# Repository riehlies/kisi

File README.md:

# kisi – quick signal and power integrity checks for KiCad

kisi reads a KiCad layout (`.kicad_pcb` + `.kicad_pro`) and checks trace impedance, high-speed channels
(loss, return loss, TDR, vias, crosstalk, skew, eye) and power delivery (regulator chain, DC IR drop,
PDN impedance, temperature estimate) – in the browser, with no installation and no setup beyond the board file.

**[Try it in your browser](https://riehlies.github.io/kisi/)** with two example boards, or open your own board
(it is processed locally and never uploaded).

> **Status.** kisi is a quick project, meant to be helpful: a fast check of a board without long setup times.
> Results are estimates for design checks, without any warranty of correctness – not a replacement for
> sign-off simulation or measurement. The individual tools – impedance map with a 2D field solver, TDR and loss
> per net, via model, crosstalk scan, power tree, IR drop, PDN per IC, temperature estimate – are useful on their
> own. kisi stays a fast linear checker – IBIS, AMI and equalisers are out of scope; for sign-off, export the
> channel to PyBERT or a circuit simulator ([why kisi is fast, and its scope](docs/models.md#why-kisi-is-small-and-fast)).

## What you get
- **Impedance:** every track against its target (from net class names such as `50Z`, `90Z_Diff`), with formulas
  in a second and the 2D field solver on demand; impedance along the path, loss, TDR, vias and crosstalk per net;
  every impedance and via result with its accuracy level (field solver, formula, estimate) and typical deviation;
  optionally fab stackup templates as a what-if for all views and the impedance band for manufacturing tolerances
  ([Fab stackups and tolerances](docs/preparing-a-board.md#fab-stackups-and-tolerances-option)).
- **Channel:** buses and device-to-device lanes through series resistors and AC-coupling capacitors, checked
  against interface profiles (PCIe, USB, DDR, LVDS, Ethernet, …) on loss, return loss, skew and a linear eye;
  differential pairs as 4-ports, multi-drop lines at every receiver, connectors with the channel behind them; a
  lane or a whole bus exported as SPICE subcircuits, Touchstone and a KiCad project for circuit simulators.
- **Preparation:** "Prepare PCB" is a checklist of what the board file lacks per category (impedance, channel,
  power): forms for the simple values, Apply per step, and `<board>.kisi.json` saved at the end; the kisi-prepare
  skill does the datasheet research.
- **Power:** the regulator chain and power flow from fields on the parts (`PI_REG`, `PI_LOAD`), DC voltage drop
  per rail and in the ground return, a losses map, a temperature estimate of the board and its parts, and the PDN
  impedance seen from every IC with recommendations.

<table>
<tr><td width="50%" valign="top"><br><b>Net detail:</b> impedance along the path, loss, TDR with the vias as physics-based models, skew of pairs and crosstalk from the neighbouring tracks – for every net with a target</td><td width="50%" valign="top"><br><b>Channel check:</b> buses and lanes from IC to IC or to a connector through series resistors and AC-coupling capacitors, judged against interface profiles on loss, return loss, skew and a linear eye – pairs as 4-ports with mode conversion, multi-drop lines per receiver (at a connector with the end and the channel behind it that you set)</td></tr>
<tr><td width="50%" valign="top"><br><b>Power flow:</b> from the supply inputs through every regulator to the loads, with regulator, shunt and copper losses</td><td width="50%" valign="top"><br><b>Voltage drop and PDN:</b> DC drop and current density on every layer of a rail, and its impedance seen from an IC with the decoupling capacitors ranked by loop inductance</td></tr>
<tr><td width="50%" valign="top"><br><b>Temperature (estimate):</b> the board's temperature per layer from the losses, the hottest parts with their junction temperature and the heat through the vias</td><td width="50%" valign="top"><br><b>Parts at temperature:</b> junction and case temperature against Tj max, with the thermal resistances used and where they come from (datasheet or package estimate)</td></tr>
</table>

## Quick start
- **Browser:** the [live version](https://riehlies.github.io/kisi/), or `kisi.html` from the
  [latest release](https://github.com/riehlies/kisi/releases/latest), offline. Drop the `.kicad_pcb` with the
  `.kicad_pro` (and `<board>.kisi.json` if there is one). KiCad 6 to 10.
- **KiCad:** the plugin `kisi-kicad-<version>.zip` from the release (KiCad's Plugin and Content Manager → *Install
  from File…*) adds a button to the PCB editor that opens the board in the viewer, with its `<board>.kisi.json`,
  and saves that file from the viewer directly next to the board – see [Getting started](docs/getting-started.md#from-kicad-the-plugin).
- **Command line** for scripts, CI and agents (Node.js ≥ 18; every command prints JSON):
  ```sh
  curl -fsSLO https://github.com/riehlies/kisi/releases/latest/download/kisi.mjs
  node kisi.mjs gaps   board.kicad_pcb     # what the analyses miss
  node kisi.mjs check  board.kicad_pcb     # channel check of all interfaces
  ```
- **Agents:** Claude Code `/plugin marketplace add riehlies/kisi` – the skills *kisi-prepare* (research missing
  data into `<board>.kisi.json`) and *kisi-si-pi-review*; other agents can follow the same `SKILL.md` files.

## Documentation
- [Getting started](docs/getting-started.md) – release files, the viewer's views, first commands
- [Preparing a board](docs/preparing-a-board.md) – the gap list, `<board>.kisi.json`, a worked example
- [Field and kisi.json reference](docs/reference.md) – net class names, `PI_*` fields, every kisi.json key
- [Models and limits](docs/models.md) – how kisi computes, accuracy, validation, estimates
- [CLI reference](docs/cli.md) – every command and option
- [Using kisi with agents](docs/agents.md) – skills and setup

All of it as one PDF: `kisi-docs.pdf` on every [release](https://github.com/riehlies/kisi/releases/latest).

## Limits
- The channel check is a first look: linear transmitter and receiver from the interface profile, no IBIS models,
  equalisation, jitter or noise.
- 2D cross-sections and reduced via and plane models instead of a full-board 3D solution.
- Validated against 620 cross-sections in CST and HFSS cases (field solver and formulas) and against 3D FDTD
  references of vias, pairs and plane cavities, each cross-checked with openEMS and CST; validation against
  measurements is still open. Data the board file lacks defaults to estimates until `<board>.kisi.json` fills
  it in. Details: [Models and limits](docs/models.md).

## Development
Build, checks and rules: [AGENTS.md](AGENTS.md) · structure: [ARCHITECTURE.md](ARCHITECTURE.md) · contributing:
[CONTRIBUTING.md](CONTRIBUTING.md) · planned work: [ROADMAP.md](ROADMAP.md) · field solver upstream:
[UPSTREAM.md](UPSTREAM.md).

## Related tools
- [js_2d_fields](https://github.com/Ttl/js_2d_fields) – Henrik Forstén's 2D field solver in the browser, used by kisi.
- [KiPI](https://github.com/drewsum/KiPI) – power integrity for KiCad (DC drop, PDN impedance, coupled noise).
- [padne](https://github.com/atx/padne) – DC voltage drop of KiCad boards with the finite element method.
- [openEMS](https://www.openems.de) – open 3D FDTD solver, for the cases where a reduced model is not enough.

## Credits
Field solver: [js_2d_fields](https://github.com/Ttl/js_2d_fields) by Henrik Forstén (GPL-3.0).
Example boards in `kisi-examples.html`: [ThunderScope](https://github.com/EEVengers/ThunderScope) Rev5.3 (EEVengers,
hardware under CERN-OHL-P-2.0) and [LibreVNA](https://github.com/jankae/LibreVNA) (Jan Käberich, GPL-3.0), shrunk to
what kisi reads; the licence texts are embedded with them.
Fonts: Barlow, Barlow Semi Condensed and JetBrains Mono (SIL Open Font License 1.1, `web/fonts/`), embedded in the viewer.

## About
kisi is a side project by David Riehl. It started as a visualisation tool for the course *Advanced PCB Design* at
TU Darmstadt and grew into a general check for KiCad boards. It was also an experiment in what current AI models
make possible: kisi was written with an AI coding assistant (Claude, Anthropic) – without it, a tool of this scope
would not have been possible as a side project. Commits made with AI help say so in their `Co-Authored-By` line.

Copyright © 2026 David Riehl and kisi contributors. Licence: GPL-3.0-only (`LICENSE`).

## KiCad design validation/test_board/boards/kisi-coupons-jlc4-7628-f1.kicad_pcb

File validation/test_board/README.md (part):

# Measurement coupons (test boards)

Status: **design v3, prepared, not ordered.** First order (maintainer, 2026-10-30 / 31): two JLC 4-layer boards
(100 × 96 and 35 × 156 mm) and one JLC 6-layer board (50 × 132 mm) with 7628 prepreg (section 4,
`make_coupons.py --first-order`). 23 more boards stay generated for
later (JLC 4 / 6 / 8 layers with 7628 prepreg, one Aisler board, JLC 4 / 6 layers with 3313 prepreg). kisi reads all of them, their
impedances are on target with kisi's field solver, the PDN and capacitor coupons have a measurement method and a
component list, and the 3D cases are written (**not run**). The connector is the 2.92 mm Samtec
`292-J-P-EP-ST-EL-01` (40 GHz); its footprint is generated from Samtec's drawing and is a **DRAFT**, and the launch
inside it is parametric, optimised on the board side in a first kisi-fdtd step (|S11| −21 dB at worst to 40 GHz;
the connector's coax not in the model, section 2). **DRC:** KiCad 7 (the workspace has no KiCad 8) on
copies converted to KiCad 7 syntax, zones refilled: no errors, no unconnected items (section 13); the maintainer
reruns it in KiCad 8 / 9. The plan behind this is `../test_board.md`.

Goal: close the loop simulation → measurement for kisi's fast models and the 3D references (`../via_ref`). The same
coupon geometry is measured, computed with kisi-fdtd (cases generated from the same description as the KiCad board)
and with kisi (the board file itself), and all three are de-embedded the same way (IEEE P370-style 2×thru,
`../fdtd/sparam.py`).

What changed in v3 (2026-10-30): the 2.92 mm Samtec connector instead of SMA and a 40 GHz frequency plan
(section 2); the footprint generated from Samtec's drawing with plated screw holes and ground pads on top and bottom;
a parametric launch (tip, taper, pad, coplanar section, ground cut, fence) and its kisi-fdtd cases
(`fdtd/launch_<stackup>/`, `make_coupons.py --launch-cases`); the GND via walls between rows at 1.27 mm instead of
2.54 mm (closed to 40 GHz). The coupons, widths and stackups are unchanged.

What changed in v2 from v1 (commit d7a7ec8): SMA connector and a 26.5 GHz frequency plan; boards split to the JLC price
brackets; every board has its own 2×thru and all connectors are on the top side (via coupons are via–line–via);
an 8-layer set; the thin-prepreg set; PDN coupons (plane cavity, pin field with capacitors) and capacitor coupons
with a component list; a pin-wide launch with a plane opening for the thin prepreg. The single v1 3D result
(`fdtd_ref/`) belonged to the old geometry and is removed.

## 1. Files

| Path | Content |
|---|---|
| `make_coupons.py` | generator: boards, kisi configuration, 3D cases; trace widths from kisi |
| `stackups.json` | stackups with values and sources (JLC 4 / 6 / 8 layers, Aisler assumed, thin prepreg) |
| `connectors.json` | Samtec 2.92 mm edge launch with sources and the drawing's dimensions, footprint parameters (**DRAFT**), launch parameters (to be optimised), layout pitches, via sizes, capacitor land patterns, size limits |
| `boards/<board>.kicad_pcb`, `.kicad_pro` | KiCad 8 boards (KiCad 9 opens them); net classes `50Z`, `100Z_Diff` |
| `boards/kisi_coupons.pretty/`, `boards/fp-lib-table` | the footprints the boards use (the Samtec launch per width, the capacitor land patterns, the IC pin fields), generated with the boards, as a project-local library (`${KIPRJMOD}`): KiCad finds them and DRC's library check matches |
| `boards/<board>.kisi.json` | kisi configuration: dielectric values with sources, class targets and profiles |
| `boards/<board>.manifest.json` | coupons, nets, connectors (J numbers, port order), parts (C/U refs), 3D cases and their cell counts |
| `boards/<stackup>.design.json` | trace widths and the impedance table (kisi formula and field solver) |
| `boards/<board>.kisi_check.json`, `kisi_check.md` | kisi run on every board (section 9) |
| `fdtd/<board key>/*.json` | kisi-fdtd cases, format of `../fdtd/via_cases.py`; run with `../fdtd/run_refs.py` |
| `fdtd/launch_<stackup>/*.json` | launch optimisation cases (section 2) |
| `fdtd_ref/launch_<stackup>/<case>/` | kisi-fdtd results of the launch cases (`kisi.s2p`, `meta.json`; section 2) |
| `check_coupons.py` | runs kisi on the boards → `kisi_check.md` |
| `compare_measured.py` | measured vs kisi vs kisi-fdtd (section 12) |
| `cst_launch.py`, `compare_launch.py`, `README_cst_launch.md` | CST Studio Suite model of the whole connector launch with Samtec's STEP model (not in the repository), compared with kisi-fdtd and Samtec's report (section 2) |

## 2. Connector, launch and frequency plan

### Connector

- **Samtec `292-J-P-EP-ST-EL-01`** (decided 2026-10-30, on the RF group's advice): 50 Ω 2.92 mm (K) jack, edge
  launch, solderless compression mount (field replaceable), performance to **40 GHz**, PCB thickness .040–.100 in
  (1.02–2.54 mm, option `-01`: every board fits, the 2.05 mm 8-layer board included), two #1-72 socket-head screws
  with #1 split washers (1/16 in hex key), **0.5–0.8 in-lb**; intermates with 3.5 mm and SMA. Why: orderable at
  DigiKey (in stock, maintainer 2026-10-30) and Mouser, solderless and reusable. Price 52.65 USD for one (Samtec, 2026-10-30). Needed:
  **4** (2 per 2-port coupon, 4 for the 4-port coupons; they move between coupons), a fifth as a spare. Sources and
  the drawing's dimensions: `connectors.json` (`connector`).
- Data from Samtec (supplied by the maintainer 2026-10-30, **not in the repository**: the terms of the SnapMagic
  footprint and the CADENAS STEP model forbid redistributing the models; the drawing is proprietary): drawing
  292-J-P-EP-ST-EL-01-X-MKT rev C, SnapMagic KiCad footprint and symbol, CADENAS STEP model, RF Characterization
  Report (2023-06-01). Samtec has no CST / HFSS model of the part.
- From the drawing and the STEP model: launch pin Ø0.18 mm (.007 in), 0.74 mm beyond the reference plane (the board
  edge), its axis 0.13 mm above the board, in a Ø0.70 mm opening of the body's front lip; the top jaw covers the
  board 5.08 mm deep and 9.53 mm wide, with a slot over the trace (2.67 mm wide from 0.38 mm, 3.18 mm from 0.64 mm,
  open to the top); the lower plate clamps the bottom side; screws 2.79 mm from the edge, ±2.92 mm.

### Footprint (generated, DRAFT)

`make_coupons.py` writes the footprint `kisi_coupons:Samtec_292-J-P-EP-ST-EL-01_EdgeLaunch_W<launch width>` (one per
launch geometry) from the parameters in `connectors.json` (`footprint`), on the boards and into the project-local
library `boards/kisi_coupons.pretty` (with `boards/fp-lib-table`, `${KIPRJMOD}`); its geometry follows Samtec's
drawing (sheet 2, "recommended footprint"):

| Feature | Drawing | Footprint |
|---|---|---|
| Screw holes | 2X Ø.0810 in, 2X .1100 in from the edge, 2X .230 in apart | Ø2.06 mm plated, GND, 2.79 mm from the edge, ±2.92 mm; Ø2.7 mm pad on every copper layer |
| Ground pads | .2550 in deep, .414 in overall, inner edges .114 in apart, 45° chamfers from .205 in to .314 in, fingers .025 in deep, .0220 in apart at the edge | the same, on the top and bottom copper (where the jaws clamp; Samtec's model has them on every layer: our planes do that inside, and PWR islands stay clear), mask open both sides (+0.05 mm) |
| Signal pad | .0205 in wide (0.52 mm), tip .0090 in (0.23 mm) | our launch (below): by default the launch width to the edge; Samtec's 0.23 mm tip tapering over 0.85 mm (taper length from the SnapMagic model) as an option |
| Edge | copper to the edge | pulled back 0.2 mm (JLC rule): the pin still rests 0.54 mm on the tip, the lip 0.18 mm on the fingers |
| Body, courtyard | body .375 in wide | Fab: body 9.53 mm wide, 5.08 mm on the board, 11.57 mm outside; courtyard ±5.51 mm, 6.73 mm on the board |

The generator checks that no copper of another net lies under the ground pads (top / bottom) and that PWR islands
keep clear of the screw holes. The finger contour (0.84 mm half-width at 0.64 mm, 0.35 mm at 0.45 mm) and the taper
length come from the SnapMagic footprint, not from dimensions on the drawing.

### Launch (parametric, first optimisation step)

Samtec's general signal pad (0.52 mm wide, 1.19 mm from the ground pads, 6.48 mm long) is 43.5 Ω on the 0.21 mm 7628
prepreg (kisi field solver): Samtec states the footprint is not optimised for electrical performance. Our launch
inside the same ground pads (`connectors.json` `launch`, `null` = the stackup's designed launch); the defaults are the
best of the first kisi-fdtd runs below:

| Parameter | Default (7628 / 3313) | Meaning |
|---|---|---|
| `tip_w`, `taper_len` | `null` (the launch width to the edge), 0.85 mm | an optional narrower tip at the edge tapering to the pad width (Samtec: 0.23 mm; a sweep point) |
| `pad_w`, `pad_len`, `pad_gap` | = launch: 0.315 mm, no extra pad, gap 0.3 mm / 0.255 mm, gap 0.105 mm | an optional wider pad (Samtec: 0.52 mm × 6.48 mm, gap 1.19 mm) |
| `w`, `gap` (design) | 0.315 / 0.3 mm (50.0 Ω) / 0.255 / 0.105 mm with the In1 opening (50.05 Ω) | the grounded coplanar launch |
| `launch_length` | 6.48 mm | to the end of the ground pads, then the coupon's 50 Ω line |
| `gnd_cut` | none / the design's In1 opening (0.465 mm) over the whole launch | an opening in the first plane under the tip / pad |
| `fence` | 0.55 mm pitch from 0.5 mm, two rows 0.4 / 1.2 mm off the gap, none within 0.45 mm of a screw hole | GND vias into all planes (0.55 mm: hole-to-hole 0.25 mm, the DRC minimum) |

The pin (Ø0.18 mm) rests on the 0.315 mm launch on 7628 and on the 0.255 mm launch on 3313. The top ground is the
union of the Samtec ground pads and the coplanar pours. The outer fence row (1.66 mm off the centre) lies in the
ground pads, where the mask is open and the jaw edge (slot wall at 1.59 mm) presses: open via holes in the contact
area are harmless electrically; if the jaw should sit on flat copper, order plugged vias or move that row inside
1.45 mm (a fence parameter). Change the values and run `make_coupons.py --reuse-design` (the boards, manifests and 3D
cases are rewritten in seconds).

### Launch optimisation (kisi-fdtd)

`make_coupons.py --launch-cases jlc4_7628 [--fdtd-exe …]` writes `fdtd/launch_jlc4_7628/`: the board from its edge to
the end of the launch plus 2.5 mm of the 50 Ω microstrip, the ground pads top and bottom, the plated screw holes,
the fence, the mask, port 1 a lumped 50 Ω port at the edge (tip to In1; under a ground cut In1 keeps a 0.25 mm strip
at the edge), port 2 at the end of the microstrip. The 7628 top prepreg is the same on the 4-, 6- and 8-layer boards,
so one stackup serves the first order (the planes below In1 differ; check the result on the 6- and 8-layer stacks).

- **Not modelled:** the connector's coax (kisi-fdtd has z-directed cylinders and horizontal sheets only): the edge
  port stands in for it, so the cases optimise the board side. `pin` adds the pin as a strip on the tip; `body` the
  top jaw (sheets with its slot, posts, the lip). CST with Samtec's STEP model and a waveguide port on the 2.92 mm
  interface checks the whole transition: `cst_launch.py` builds it (`README_cst_launch.md`; the connector from primitives with the STEP's dimensions; a first run with the imported STEP failed, to be run again).
- **Target:** |S11| < −20 dB to 40 GHz for one launch (Samtec's own optimised fixture on MT40: −23 to −25 dB for one
  connector with 500 mil of trace, report 2023-06-01).
- **Results (2026-10-30, `fdtd_ref/launch_jlc4_7628/`):**

  | Case | What | max \|S11\| 0.5–40 GHz | \|S11\| at 10 / 20 / 30 / 40 GHz | \|S21\| at 40 GHz (≈ 9 mm) |
  |---|---|---|---|---|
  | `default` | launch width to the edge, fence 0.55 mm | **−21.0 dB** at 36.5 GHz | −29.8 / −28.5 / −28.6 / −25.0 dB | −0.75 dB |
  | `notip_f05` | the same, fence 0.5 mm | −21.0 dB at 36.4 GHz | −29.9 / −28.5 / −28.7 / −25.0 dB | −0.75 dB |
  | `notip_f08` | the same, fence 0.8 mm from 0.8 mm (first draft) | −18.9 dB at 36.8 GHz | −29.9 / −28.4 / −29.1 / −22.2 dB | −0.84 dB |
  | `tip023_f08` | Samtec's 0.23 mm tip, fence 0.8 mm | −15.7 dB at 37.2 GHz | −38.0 / −30.5 / −19.9 / −15.7 dB | −0.93 dB |
  | `tip023_pin_f08` | the same with the pin | −16.8 dB at 37.0 GHz | −35.6 / −33.2 / −22.1 / −17.3 dB | −0.90 dB |
  | `samtec` | Samtec's pad (0.52 mm, gap 1.19 mm, 0.23 mm tip), fence 0.8 mm | −14.6 dB at 24.8 GHz | −26.6 / −19.7 / −19.5 / −22.0 dB | −1.19 dB |
  | `default_body`, `samtec_cut` | with the jaw; Samtec's pad over an In1 cut | not valid yet / not run | | |

  Reading: our 50 Ω coplanar launch inside the Samtec pads meets the target on the board side (−21.0 dB worst). The
  0.8 mm fence left narrow \|S21\| dips at 25.5, 27, 35.5 and 37.5 GHz (resonances of the fence / screw-hole region);
  0.55 mm from 0.5 mm removes them (and halves the ringing: 12 800 instead of 23 200 steps). Samtec's 0.23 mm tip is
  inductive on 7628 even with the pin over it (−16.8 dB); Samtec's general pad is not usable on the 0.21 mm prepreg
  (−14.6 dB, and its sparse fence – the rows move out to the screw holes – lets the plane-pair mode carry power
  away: \|S21\| −2 dB already at 1 GHz). Values below about 2 GHz are limited by the edge port (−24 dB at 1 GHz on
  every case). `default_body` (the jaw) ran twice (as `ours_body`) and is **not valid yet**: port 1 sees a near short
  (\|S11\| about 0 dB at low frequency, \|S21\| −30 dB at 1 GHz rising to −2.7 dB at 40 GHz), also after moving the
  jaw's underside to the copper height and its top off the domain boundary – the jaw approximation needs debugging.
- **Other stacks** (the `default` case written with `launch_case` for each, not stored): jlc6-7628 and jlc8-7628
  give the same −21.0 dB at 36.5 GHz (the same 7628 top prepreg; the planes below In1 do not matter here), so the
  first order's 6-layer boards share the 4-layer launch. jlc4-3313 (the pin-wide 0.255 mm launch over the In1
  opening): −16.7 dB at 34.5 GHz – to be optimised before a 3313 order.
- **Run time:** 0.9–1.0 M cells: 120–680 s per case on this workspace (2 vCPUs shared with other jobs); the jaw cases
  (2.1–2.3 M cells) about 950 s.
- **Next:** fix the jaw case; the coplanar `gap` 0.2–0.4 mm with `w` re-solved for 50 Ω, `launch_length` 3–6.48 mm, a
  cut in In1 under the edge (0.3–0.8 mm wide, 0.3–1.0 mm long), the fence row offset; the 6- and 8-layer stacks; the
  thin-prepreg (3313) launch (`--launch-cases jlc4_3313`); then CST with the STEP model for the whole connector.

### Frequency plan (2.92 mm, 40 GHz)

kisi's stub resonance for the stubbed vias (`kisi_check.md`):

| Coupon | Stub | kisi stub resonance | In the 40 GHz band? | v3 |
|---|---|---|---|---|
| 6 layers VLV_L3, SL_L3 (L1 → In2, stub to L6) | 0.88 mm (3313: 0.82) | 32.4 GHz (34.5) | **yes** (v2: no) | the notch is now measured on the 6-layer board too (PNA-X, PNA) |
| 6 layers DIFF_SL, BS_L3L4 (inner exits) | 0.65–0.88 mm | 24.5–38 GHz | yes (v2: partly) | coupling coupons, read in the time domain |
| 8 layers VLV_L3, SL_L3 (L1 → In2, stub to L8, 2.05 mm board) | 1.42 mm | 19.8 GHz | yes | inside the band of every VNA, the 20 GHz ENA included |
| 8 layers E_L1L3 (pair, stub to L8) | 1.42 mm | 22.1 GHz | yes | differential stub notch |
| 8 layers VLV_L6 (L1 → In5, stub to L8) | 0.60 mm | 38.5 GHz | **yes**, at the top (v2: no) | short-stub reference; its notch now just inside the band |

- **2.0 mm 8-layer board:** with 40 GHz, a 1.6 mm 8-layer board (about 1.1 mm of stub, notch near 25 GHz) would now be
  inside the band too; the 2.0 mm board stays (a lower, deeper notch that the 20 GHz ENA sees as well; within the
  connector's 2.54 mm limit). Not changed.
- **Row walls:** at 2.54 mm the GND via walls between rows open near 28 GHz (pitch = λ/2 in FR-4); v3 uses 1.27 mm
  (λ/2 near 56 GHz). The launch fence (0.8 mm, below λ/4 at 40 GHz) and the CPWG fence (1.0 mm, below λ/2) stay.
- **TRL:** LINE_27 (ΔL 2 mm) reaches 160° near 37 GHz; the multiline set (ΔL 2 / 5 / 10 / 25 / 75 mm) stays usable to
  40 GHz with LINE_30 and LINE_50.
- **3D cases:** already computed to 40 GHz (section 7), unchanged.
- Everything else (lines, through vias, return path, pairs without stubs, coupling) has no stub resonance below
  40 GHz; the plane cavities resonate at 1.4–3.2 GHz (measured to 8 GHz).

## 3. Stackups

Values fetched on 2026-10-22; sources in `stackups.json` (key `sources`): thicknesses from JLC's impedance-template
data ([gsuberland/jlcpcb_autogenerated_stackups](https://github.com/gsuberland/jlcpcb_autogenerated_stackups), commit
9c8b685), 7628 / 3313 / 2116 εr from [JLC capabilities](https://jlcpcb.com/capabilities/pcb-capabilities), core εr
4.6 from [JITX's JLC materials](https://docs.jitx.com/en/latest/_modules/jitxlib/jlcpcb/materials.html), tan δ 0.02
assumed (not published), mask εr 3.8 and 1.2 mil from the
[JLC impedance calculator guide](https://jlcpcb.com/help/article/user-guide-to-the-jlcpcb-impedance-calculator).

| Stackup | Order | Dielectrics L1 → bottom (mm) | Copper | Planes / signal layers |
|---|---|---|---|---|
| **JLC04161H-7628** | first | 7628 0.2104 · core 1.065 · 7628 0.2104; 1.586 total | 1 oz outer, 0.5 oz inner | GND In1, In2 (PDN: PWR islands on In2) / L1, L4 |
| **JLC06161H-7628** | first | 7628 0.2104 · core 0.4 · 7628 0.2104 · core 0.4 · 7628 0.2104; 1.562 | same | In1, In4 / L1, In2, In3, L6 |
| **JLC08201H-7628** | first | 7628 0.2104 · core 0.35 · 7628 · core 0.35 · 7628 · core 0.35 · 7628; 2.053 | same | In1, In3, In4, In6 (PDN: PWR islands on In3 over In4, 0.35 mm) / L1, In2, In5, L8 |
| Aisler 4 layers 1.6 mm (**assumed**) | first | prepreg 0.2 · core 1.2 · prepreg 0.2 (εr 4.3 / 4.5 / 4.3) | 35 µm | as JLC 4 layers |
| **JLC04161H-3313** | second | 3313 0.0994 · core 1.265 · 3313 0.0994; 1.564 | 1 oz / 0.5 oz | as JLC 4 layers |
| **JLC06161H-3313** | second | 3313 0.0994 · core 0.55 · 2116 0.1164 · core 0.55 · 3313 0.0994; 1.546 | same | as JLC 6 layers |
| JLC08161H-2116 | – | in `stackups.json`, not generated (1.6 mm 8 layers: stub only about 1.1 mm) | | |

The 7628 top prepreg is the same on the 4-, 6- and 8-layer boards (and on LibreVNA), so the launch and the L1 lines
are identical on all first-order JLC boards: a build-to-build check. The Aisler stack is the generic `s4` of the
3D references until Aisler sales give the real one; its line and cavity coupons extract it.

## 4. Boards

### First order (maintainer, 2026-10-30 / 31)

Only JLC 4 layers (JLC04161H-7628) and JLC 6 layers (JLC06161H-7628), three boards; the other boards below stay
generated for later. An edge launch takes 12 mm of board edge per connector and side (rows of 12 mm, 4-port rows
24 mm), so a 96 mm board holds 16 connector positions: the 4-layer coupons need 38 (with a 2×thru on each board) and
need two boards, one of them above the 100 × 100 mm bracket; the 6-layer board is one board above the 50 × 50 mm
bracket (accepted). One 2×thru per board (PAIR is the E coupons' fixture). `make_coupons.py --first-order` writes
only these. Sizes are the bounding boxes of the stepped outlines (what JLC's calculator asks for):

| Board | Size (mm) | Thickness | Coupon | What | 3D reference cases |
|---|---|---|---|---|---|
| **jlc4-7628-f1** | **100 × 96** | 1.59 mm | THRU | 2×thru L1 (fixture of this board) | thru_s4_L1 |
| | | | CPWG_25, CPWG_50 | grounded coplanar line, L and 2L (εr, tan δ, roughness by line–line) | T_vna6_cpwg_10 / _20 |
| | | | XT_MS | edge-coupled microstrip aggressor / victim (4-port) | T_ts6_xt_ms_s10 |
| | | | G_CAV | plane cavity 50 × 30 mm, two ports (shunt-thru) | G_pp100 / pp200 |
| **jlc4-7628-f2** | **35 × 156** | 1.59 mm | THRU | 2×thru L1 | thru_s4_L1 |
| | | | A0800, A1000, A1200 | coax section L1 → L4 → L1, antipad Ø0.8 / 1.0 / 1.2, 4 GND vias at 1 mm | A_s4_d300_ap800 / ap1000 (1.2: none) |
| | | | D_S0p7, D_S2p0, D_NONE | return via 0.7 / 2 mm from each via / none, L1 (ref In1) → L4 (ref In2) | D_s8_stitch_0p5 / 2p0 / none |
| | | | PAIR | pair 2×thru at the 1.0 mm via pitch (fixture of E) | – |
| | | | E_R_G2, E_R_G0 | differential via pair L1 → L4 → L1, round antipads, 2 / 0 GND vias (4-port) | E_s8_L1L8_p1000_round_g2 / g0 |
| **jlc6-7628-f1** | **50 × 132** | 1.56 mm | THRU | 2×thru L1 | thru_s4_L1 |
| | | | SL_L3, VLV_L3 | 25 mm stripline on In2 (L3) and the 5 mm version: line–line = the stripline 2×thru; VLV_L3 is also the via with stub (to L6, notch 32 GHz) | T_ts6_sl_10 / _20, B_ts6_L1L3_stub, B_s8_L1L3_stub_d300 |
| | | | B_L1L6 | through via without stub | B_ts6_L1L6, B_s8_L1L8_d300 |
| | | | PAIR, E_R_G2 | pair 2×thru; pair L1 → L6 → L1, 2 GND vias | E_s8_L1L8_p1000_round_g2 |
| | | | D_S0p7, D_S2p0, D_NONE | return via 0.7 / 2 mm / none, L1 (ref In1) → L6 (ref In4) | D_s8_stitch_0p5 / 2p0 / none |

The lines, the coupling coupon and the cavity share the 100 mm-wide board (the cavity row sets its width anyway);
the via groups stay together on one board, so A, D and E are compared within one panel.

- **0.5 mm return via:** made at 0.7 mm. With the 0.3 / 0.6 mm vias the pads would overlap at 0.5 mm (the 3D
  reference D_s8_stitch_0p5 is idealised: a bare barrel); 0.7 mm keeps 0.1 mm between the pads (JLC) and puts the
  GND barrel just outside the Ø0.8 antipad. The 3D case of D_S0p7 has the 0.7 mm geometry.
- **8-layer board:** the 6-layer stub notch (VLV_L3, kisi 32.4 GHz; 3D reference B_ts6_L1L3_stub) is inside the
  40 GHz band, so the first order measures a stub notch without the 8-layer board. The 8-layer long-stub board
  (notch near 20 GHz, deeper, also within the 20 GHz ENA) stays for later.
- **Later (generated, not in the first order):** the PDN loop and capacitor coupons (assembly: jlc4-7628-p, -d,
  jlc8-7628-p), Aisler, the 3313 thin-prepreg boards, the 8-layer boards, and the other JLC 4 / 6-layer coupons
  (microstrip lines and the TRL set, oval antipad, D at 1 / 3.5 mm, broadside, stripline pair: jlc4-7628-a … -d,
  jlc6-7628-a … -d).
- **DRC** (KiCad 7 on converted copies, section 13): no errors, no unconnected items on the three boards.

### All boards

Limits (maintainer, 2026-10-22, JLC price brackets): 4 layers ≤ 100 × 100 mm, 6 and 8 layers ≤ 50 × 50 mm; the
generator refuses a JLC board that exceeds them. Aisler charges by area: one dense board of 35 mm rows.
Rows are sorted by length (a stepped outline); a row is one coupon from edge to edge, or two coupons side by side
with their ports on the outer edges (PDN coupons). 2-port rows are 12 mm, 4-port rows 24 mm (two connectors per
edge, 12.7 mm apart). GND via walls (1.27 mm, through all layers; v2: 2.54 mm) run along every row boundary and along the
exposed step edges. Through vias only, drill 0.3 / pad 0.6 mm, inner non-functional pads removed. Antipads, island
clearances and the launch openings are KiCad keep-out rule areas, so a refill reproduces them. Bottom silk: board
name, template, date and JLC's order-number placeholder `JLCJLCJLCJLC`.

| Board | Layers | Size (mm) | Coupons |
|---|---|---|---|
| **kisi-coupons-jlc4-7628-a** | 4 | 100 × 96 | THRU, LINE_27, LINE_30, LINE_50, LINE_100, REFLECT, CPWG_25, CPWG_50 |
| **kisi-coupons-jlc4-7628-b** | 4 | 35 × 96 | THRU, A0800, A1000, A1200, D_S1p0, D_S2p0, D_S3p5, D_NONE |
| **kisi-coupons-jlc4-7628-c** | 4 | 35 × 96 | PAIR, E_R_G2, E_O_G2, E_R_G0 |
| **kisi-coupons-jlc4-7628-d** | 4 | 50 × 96 | THRU, CAPZ_0402, CAPZ_0603, CAPZ_0805, XT_MS, DIFF_MS |
| **kisi-coupons-jlc4-7628-p** | 4 | 100 × 96 | THRU, G_CAV, H_D2, H_D5, H_D10, H_D20 |
| **kisi-coupons-jlc6-7628-a** | 6 | 35 × 48 | THRU, B_L1L6, D_S1, D_NONE |
| **kisi-coupons-jlc6-7628-b** | 6 | 50 × 48 | THRU, VLV_L3, SL_L3, LINE_50 |
| **kisi-coupons-jlc6-7628-c** | 6 | 35 × 48 | PAIR, E_R_G2 |
| **kisi-coupons-jlc6-7628-d** | 6 | 50 × 48 | BS_L3L4, DIFF_SL (no 2×thru: section 5) |
| **kisi-coupons-jlc8-7628-a** | 8 | 50 × 48 | THRU, VLV_L3, B_L1L8, SL_L3 |
| **kisi-coupons-jlc8-7628-b** | 8 | 35 × 48 | THRU, VLV_L6, D_S1, D_NONE |
| **kisi-coupons-jlc8-7628-c** | 8 | 35 × 48 | PAIR, E_L1L8 |
| **kisi-coupons-jlc8-7628-d** | 8 | 35 × 48 | PAIR, E_L1L3 |
| **kisi-coupons-jlc8-7628-p** | 8 | 50 × 48 | H_D2, H_D5, H_D10, H_D2_0603 (no 2×thru: section 5) |
| **kisi-coupons-aisler4-assumed-a** | 4 | 35 × 144 | THRU, LINE_27, LINE_30, LINE_35, A0800, A1000, A1200, D_S1p0, D_S2p0, D_NONE, G_SMALL |
| kisi-coupons-jlc4-3313-a … -d | 4 | as jlc4-7628-a … -d | the same coupons on the thin prepreg (CAPZ: the mounting inductance with 0.1 mm to the plane) |
| kisi-coupons-jlc6-3313-a … -d | 6 | as jlc6-7628-a … -d | the same coupons on the thin prepreg |

Besides the first order (above): 14 JLC 7628 boards and the Aisler board, and 8 JLC 3313 boards, generated for later.

### Coupons

| Coupon | Length (mm) | What | Validates in kisi | 3D reference | 3D window |
|---|---|---|---|---|---|
| THRU | 25 | 2×thru on L1, reference planes 12.5 mm from each edge | fixture of every 2-port coupon on the board; TRL thru | thru_s4_L1 | w10 |
| LINE_27 / 30 / 35 / 50 / 100 | 27–100 | 50 Ω microstrip, ΔL 2 / 5 / 10 / 25 / 75 mm against THRU | εeff, loss per mm, Zc (line–line); multiline TRL | T_ts6_ms | LINE_50 w10 / w20 |
| REFLECT | 30 | two open ends at the reference planes | TRL reflect | – | – |
| CPWG_25, CPWG_50 | 25, 50 | grounded CPW on L1, gap 0.18 mm (LibreVNA), fence 1.0 mm | CPWG Zc and εeff (formula εeff +5 % vs 3D) | T_vna6_cpwg | w10, w20 |
| A0800 / A1000 / A1200 | 30 | via–line–via L1 → L4 → L1 through the plane pair, antipad Ø0.8 / 1.0 / 1.2, 4 GND vias at 1 mm | via ladder: antipad dependence of Z and delay | A_s4_d300_ap800 / ap1000 | wv |
| D_S1p0 / S2p0 / S3p5 / NONE | 35 | L1 (ref In1) → L4 (ref In2) → L1, one GND via at 1 / 2 / 3.5 mm from each via, none | return path of a reference change (GND vias within 3 mm enter the ladder, up to 5 mm an inductance, beyond "missing") | D_s8_stitch_* | wv |
| B_L1L6, B_L1L8 | 30 | through via, no stub (via–line–via on the bottom layer) | via ladder through several planes | B_ts6_L1L6, B_s8_L1L8_d300 | wv |
| VLV_L3 (6, 8 layers), VLV_L6 (8) | 30 | via–line–via to an inner layer, stub to the bottom | junction model, stub capacitance / notch (section 2) | B_*_L1L3_stub, X_s8x2_L1L3_bd | wv |
| SL_L3 | 50 | the same with 25 mm stripline | stripline γ (line–line with VLV_L3: the vias cancel), Zc from the TDR plateau | T_ts6_sl | w10, w20 |
| PAIR | 30 | pair 2×thru on L1 at the 1.0 mm via pitch (100 Ω diff.), 15 mm per side | fixture of the pair coupons on the board | – | w6 |
| E_R_G2 / E_O_G2 / E_R_G0 / E_L1L8 / E_L1L3 | 35 | pair via–line–via, pitch 1.0, round / oval antipads, 2 / 0 GND vias; E_L1L3 with stubs | pair ladder: Sdd21, Zdiff, Scd21, oval antipad, differential stub | E_s8_L1L8_p1000_*, E_s8_L1L3 | wv |
| XT_MS | 50 | 50 Ω aggressor and victim on L1, edge gap = w | NEXT / FEXT (kisi's NEXT 70–80 % high vs 3D) | T_ts6_xt_ms_s10 | wc |
| DIFF_MS, DIFF_SL | 50 | 100 Ω edge-coupled pair on L1 / In2 | Zdiff (TDR plateau), odd-mode εeff | T_ts6_diff_ms / _sl | wc |
| BS_L3L4 | 50 | broadside In2 over In3 | broadside NEXT / FEXT (kisi lists, does not compute yet) | T_ts6_broadside_o0 | wc |
| CAPZ_0402 / 0603 / 0805 | 25 | capacitor footprint in shunt on the 50 Ω line, two GND vias | mounted C, ESR, ESL, mounting inductance, pad capacitance (section 6) | – | w10 (0 Ω) |
| G_CAV, G_SMALL | 100, 35 | PWR island 50 × 30 (Aisler 25 × 18) mm on In2 under In1 (JLC d = 1.065 mm, Aisler assumed 1.2 mm), ports at a corner and the centre | cavity resonances (kisi cavity model ±0.8 % vs 3D), core εr, plane capacitance | G_pp100/200 | wg |
| H_D2 / D5 / D10 / D20, H_D2_0603 | 50 (4 layers), 25 (8) | pin field + one capacitor at 2 / 5 / 10 / 20 mm, PWR island, two shunt-thru ports (section 6) | capacitor loop inductance and Z(f) at the IC (`power --pdn`) | H_s8_cap_* | wh |

The trace widths of every coupon come from `boards/<stackup>.design.json` (section 8). The G coupon's first modes
(magnetic walls, εr 4.6): 1.40 (10), 2.33 (01), 2.72 (11), 2.80 (20) GHz; kisi's cavity model gives 1.398 GHz.

## 5. De-embedding across boards

Every separately ordered board is a separate panel and process run: εr, pressed prepreg thickness, etched width and
mask thickness differ from run to run (JLC: impedance ±10 %, thickness ±10 %, track width ±20 %). A 2×thru taken from
another board carries that difference into the de-embedded coupon: a 5 % impedance difference of the 12.5 mm feeds
leaves a reflection of about −32 dB and a delay error of a few ps per side, which is the size of the effects the line
and via comparisons look for. **Decision: every board carries its own 2×thru** (THRU; PAIR on boards with 4-port
coupons), and all via coupons are **via–line–via** structures fed from L1 at both ends, so that one L1 fixture per
board serves them all and every connector sits on the top side (no bottom-side 2×thru, no connectors mounted upside
down).

Trade-off of via–line–via: each coupon has two vias. The line between them (5 mm, D group 10 mm) separates them in
the TDR (about 60 / 120 ps round trip against a 25–35 ps edge), kisi and the 3D cases compute the same two-via
structure, and the first via alone is read from the TDR. The cost is a second via in the S-parameters (|S21|
dips add up) and two more connector positions on the 4-port boards.

Exceptions, justified:
- **jlc6-7628-d / jlc6-3313-d** (BS_L3L4, DIFF_SL): no room for a THRU within 50 × 50 mm (two 24 mm rows). Both are read
  in the time domain (TDR plateau of the coupled section, NEXT / FEXT peaks), where the fan-out is separated by time;
  a THRU would not de-embed them anyway (their fixture includes the via to the inner layer).
- **jlc8-7628-p** (PDN): the shunt-thru quantities |Z|, the ESR at the series resonance and the inductance from |Z|
  do not depend on the feed delay; above about 100 MHz, Re Z does. The feeds (12.5 mm, as one half of a THRU) can be
  removed with the VNA's port extension set to the delay of the THRU of jlc8-7628-a / -b (same template, different
  panel: a few ps difference, uncritical here); `compare_measured.py` reports these coupons from the raw data.
- The coupled coupons XT_MS and DIFF_MS on the 4-layer D boards are also read in the time domain; their board has a
  THRU for the CAPZ coupons.

Within one board, all coupons share the panel, so the remaining uncertainty is the connector remount (measure THRU
three times). The 4-layer A board carries an independent check: multiline TRL with THRU, LINE_27/30/50/100 and
REFLECT on the same reference planes.

## 6. PDN and capacitor coupons

### Structures

- **H (PDN loop):** a 4 × 4 pin field at 0.8 mm (BGA-like, checkerboard PWR / GND, 0.6 mm pads with a via in every
  pad; the PWR pins are tied by a 3.2 × 3.2 mm copper patch on L1, the U footprint carries `PI_LOAD` and `PI_TARGET`
  so kisi analyses it as an IC; it stays unpopulated, so the vias in its pads need no filling), one capacitor footprint whose GND pad centre is d = 2 / 5 / 10 / 20 mm from the edge
  of the pin field, a via next to each capacitor pad, and a PWR island on the PDN layer (4 layers: In2, under the GND
  plane In1, 1.065 mm; 8 layers: In3, over the GND plane In4, 0.35 mm). The islands have the same size within a board
  (4 layers 27.7 × 21.6 mm, 8 layers 17.7 × 21.6 mm), so only the distance changes. H_D2_0603 (8 layers) is H_D2 with an
  0603 footprint. Rails `VDD_<coupon>` (0 V: no DC-bias derating, as in the unbiased VNA measurement).
- **G (cavity):** PWR island on In2 under In1, fed at a corner and at the centre through vias from L1 lines.
- **CAPZ:** a capacitor footprint (KiCad standard land pattern) from the 50 Ω line to GND with two GND vias, in 0402,
  0603 and 0805.

### Measurement method: 2-port shunt-thru

Z = 25 · S21 / (1 − S21) (Z ≪ 25 Ω; 1 mΩ gives S21 ≈ −88 dB, inside a VNA's dynamic range at IFBW 10–100 Hz).
What the structures provide:
- **Two ports per DUT, Kelvin-connected:** the H coupons have both connectors on one edge (12.7 mm apart), each with
  its own 50 Ω trace to the pin-field patch, so the only shared impedance is the DUT (patch, vias, planes, capacitor).
  The ground of both ports is the board ground (launch pours, fence vias, planes). CAPZ and G have one port per edge.
- **Feeds of 12.5 mm** per port (the H feed is 3 mm launch + 4.8 mm + 4.7 mm, the same as half of THRU), so the
  board's THRU de-embeds them in a linear sweep.
- **Settings:** two sweeps per DUT: log 100 kHz – 100 MHz (801 points, IFBW 10–30 Hz, 0 dBm) where the feeds do not
  matter, and linear 10 MHz – 2 GHz with 10 MHz steps (P370 grid, de-embedded with THRU). Calibration: SOLT / ECal at
  the cable ends.
- **Ground loop below about 1 MHz:** the shield of the port-2 cable is in parallel with the measured milliohms.
  Put a coaxial ground-loop isolator / common-mode transformer on port 2 (e.g. Picotest J2102B) or many turns of the
  cable through a high-permeability ferrite core, or use a VNA gain-phase port with an isolated receiver; check the
  floor with the 0 Ω population (the reading at 100 kHz must stay at the jumper's resistance).
- **Populate variants:** each board comes as 5 copies, so the same footprint is measured with several parts (table
  below). File names `<COUPON>.<variant>.s2p`; `compare_measured.py` extracts C, SRF, ESR, ESL / loop inductance and
  compares with kisi (H: `power --pdn` with that part as a PI_CAP; CAPZ: `data/components.json` directly – written
  when kisi's `net` ignored shunt parts; kisi 0.3.1 models them at their pads, so `net` could be compared too).

### Component list (generic; the maintainer picks parts from stock)

| Where | Copy 1 | Copy 2 | Copy 3 | Copy 4 | Copy 5 |
|---|---|---|---|---|---|
| H_D2 … H_D20 (0402) | empty | 0 Ω jumper 0402 | 100 nF X7R 16 V 0402 | 1 µF X5R/X7R 10 V 0402 | 10 nF X7R 50 V 0402 |
| H_D2_0603 (0603) | empty | 0 Ω jumper 0603 | 100 nF X7R 16 V 0603 | 1 µF X7R 16 V 0603 | 10 nF X7R 50 V 0603 |
| CAPZ_0402 | empty | 0 Ω 0402 | 100 nF X7R 16 V 0402 | 1 µF X5R 10 V 0402 | 10 µF X5R 6.3 V 0402 |
| CAPZ_0603 | empty | 0 Ω 0603 | 100 nF X7R 16 V 0603 | 1 µF X7R 16 V 0603 | 10 µF X5R 10 V 0603 |
| CAPZ_0805 | empty | 0 Ω 0805 | 100 nF X7R 50 V 0805 | 1 µF X7R 25 V 0805 | 10 µF X5R 16 V 0805 |
| U (pin field) | not a part: the pads stay bare (no BOM entry) | | | | |

Alternatives: any MLCC of the same case size (Murata GRM, Samsung CL, TDK C, Yageo CC); voltage and dielectric are
free because the measurement is unbiased (they only matter for the DC-bias part of kisi's model, which is off here);
0 Ω thick-film jumpers of any make. Quantities per order: 5 boards × (4 H or 3 CAPZ) per board type, plus spares.

What they validate in kisi (`data/components.json`, `decoupling` / `packages`):

| Data | Value now | Measured by |
|---|---|---|
| `decoupling.esl_nh` by package | 0402 0.35, 0603 0.5, 0805 0.6 nH | CAPZ (copies 3–5: ESL above the SRF, minus the 0 Ω mounting loop), H_D2 vs H_D2_0603 |
| `decoupling.esr` model k·(c_ref/C)^0.4 | 100 nF 25 mΩ, 1 µF 10 mΩ, 10 µF 4 mΩ, 10 nF 63 mΩ | CAPZ and H, ESR at the SRF |
| `decoupling.mount_nh` | 0.4 nH | CAPZ copy 2 (0 Ω): footprint + vias; 4 layers 7628 vs 3313 (0.21 vs 0.1 mm to the plane) |
| `packages.pad_c_pf` | 0402 0.1, 0603 0.15, 0805 0.2 pF | CAPZ copy 1 (empty) |
| kisi PDN: plane spreading and via inductance (`l_path`), cavity model | 4 layers: L path 2.43 → 3.70 nH (d = 2 → 20 mm); 8 layers: 0.97 → 1.11 nH (2 → 10 mm) | H copy 2 (0 Ω): Im Z / ω; G: resonances, plane capacitance |
| package from the footprint | 0805 read from the footprint name (v2: from the pad pitch, taken as 0603) | CAPZ_0805 (section 9) |

**After populating, please enter the datasheet values** of the parts actually used. For the H coupons, as PI_CAP
fields in the board's `.kisi.json` (refs in the manifest, e.g. C1 = H_D2 on jlc4-7628-p):
```json
"fields": [{"ref": "C1", "name": "PI_CAP", "value": "c=100n esr=22m esl=0.33n X7R rated=16V",
            "source": {"kind": "datasheet", "document": "GRM155R71C104KA88 data sheet / SimSurfing", "note": "0 V, 25 °C"}}]
```
For the comparison, the same values go into `MEASURED_DIR/populate.json`, one entry per variant
(`{"100n": {"part": "GRM155R71C104KA88", "pi_cap": "c=100n esr=22m esl=0.33n"}}`); without it the generic values
above are used (0 Ω as `c=1 esr=5m`, i.e. inductance only).

### kisi's prediction (generic 100 nF 0402, `kisi_check.md`)

| Board | Coupon | L path / L total (nH) | SRF (MHz) | Magnitude of Z at 100 MHz (Ω) |
|---|---|---|---|---|
| jlc4-7628-p | H_D2 / D5 / D10 / D20 | 2.43 / 3.07 · 2.70 / 3.34 · 3.04 / 3.68 · 3.70 / 4.34 | 9.1 · 8.7 · 8.3 · 7.6 | 1.95 · 2.13 · 2.35 · 2.79 |
| jlc8-7628-p | H_D2 / D5 / D10 · D2_0603 | 0.97 / 1.61 · 1.02 / 1.66 · 1.11 / 1.75 · 1.18 / 2.06 | 12.6 · 12.4 · 12.0 · 11.1 | 1.03 · 1.07 · 1.13 · 1.34 |

The thick 4-layer core makes the distance visible (+1.3 nH from 2 to 20 mm); on the 8-layer board the thin cavity
keeps it small (+0.15 nH from 2 to 10 mm), which tests the other end of the model.

## 7. 3D cases (kisi-fdtd), written, not run

Each coupon has one or more **windows**: the coupon between two port planes on the real stackup, with lumped 50 Ω ports
where traces cross the window edge, planes into the PML, the solder mask as a 0.0305 mm dielectric layer, zero-thickness
copper widened by Wheeler's Δw, thirds rule, 0.035 mm fine mesh to 40 GHz (H: 0.07 mm, 2 GHz; G: 0.1 mm, 8 GHz;
CAPZ: 20 GHz). Windows: `w10` / `w20` lines and THRU (10 / 20 mm), `wv` via–line–via with 5 mm L1 feeds (pairs 3 mm),
`w6` PAIR, `wc` coupled section, `wg` cavity, `wh` PDN loop, CAPZ `w10`. Capacitors are modelled populated with 0 Ω
(5 mΩ lumped short on a 0.5 mm body loop, as `via_cases.pdn_loop`), so the 3D result is the mounting / loop
inductance. The fixtures `THRU w10` and `PAIR w6` de-embed the 3D results with the same geometry as the measurement.

**105 cases, 0.4–2.4 M cells each, 131 M cells in total** (`fdtd_cells` in the manifests; v2: 126 M, the denser row walls add the rest); the first-order boards add 25 cases
(33 M cells, mostly copies of the same coupons); plus the launch cases (section 2). Not run here (maintainer's
decision); v1 proved the format with one case (0.75 M cells, 36–85 s on one shared core). *Estimate: 1–5 min per via
case, longer for G and H (low-frequency ringing); several CPU hours in total.*
```
cargo build --release -p kisi-fdtd
python3 validation/fdtd/run_refs.py validation/test_board/fdtd/jlc4_7628_b validation/test_board/fdtd_ref --exe target/release/kisi-fdtd --jobs 2
```
Known model limits (`../fdtd/README.md`): lossless metal, dielectric loss fixed at `f_loss`; compare losses with kisi.

## 8. Trace widths (from kisi)

Widths are solved with kisi on a probe board per cross-section (the same KiCad writer as the coupons): bisection with
the native formulas, then secant steps with the 2D field solver (`kisi.mjs`), rounded to 5 µm
(`boards/<stackup>.design.json`). Field solver values; the formula deviation in brackets:

| Cross-section | 7628 (4 / 6 / 8 layers) | 3313 (4 / 6 layers) |
|---|---|---|
| 50 Ω microstrip L1 / bottom | 0.345 mm: 49.8 Ω (+1.8 %) | 0.150 mm: 50.2 Ω (+2.8 %) |
| launch | 0.315 / gap 0.3: 50.0 Ω (+5.7 %) | 0.255 / gap 0.105, In1 opening 0.465: 50.05 Ω (**+25 %**) |
| CPWG, gap 0.18 | 0.280: 49.7 Ω (+6.9 %) | 0.140: 50.2 Ω (+6.0 %) |
| 100 Ω microstrip pair, s 0.2 | 0.205: 100.1 Ω (+4.1 %) | 0.115: 99.9 Ω (+6.8 %) |
| pair at the 1.0 mm via pitch, L1 | 0.315: 99.8 Ω (+4.3 %) | 0.150: 100.4 Ω (+2.8 %) |
| 50 Ω stripline | 6 layers In2/In3 0.405: 49.9 Ω; 8 layers In2/In5 0.210: 49.9 Ω | 6 layers 0.515: 50.1 Ω |
| 100 Ω stripline pair, s 0.2 | 6 layers 0.190: 99.8 Ω (+10.3 %); 8 layers 0.140: 100.4 Ω (+4.8 %) | 0.210: 99.9 Ω (+13.1 %) |
| Aisler (assumed) | microstrip 0.335, launch 0.305 / 0.3, CPWG 0.275, pair 0.21 / 0.2 | |

The field solver is within 1.6 % of HFSS (`../fdtd/TESTS.md`), so it sets the widths; the formula deviations are
kisi's known weak spots (coplanar, stripline pairs, and new: the launch over a plane opening) and are themselves a
target of the measurement.

## 9. kisi check (native CLI and kisi.mjs)

`check_coupons.py` ran `overview`, `config-check`, `check --all`, `interfaces`, `gaps`, `net` on every signal net and
`power --pdn` on every PDN rail, with the native `kisi` (formulas) and `kisi.mjs` (field solver), both kisi 0.3.1
(v3 run 2026-10-30 on the regenerated boards; the v2 run used 0.2.3). Full tables: `kisi_check.md`.

- All 26 boards (23 + the 3 first-order boards) parse with the stackup from the file and no board warnings; `config-check` is ok; `gaps` reports only
  the missing regulator chain (and on the PDN boards the rails without a voltage, finding 4).
- 50Z within ±5 % of the length: 93–100 % with the field solver, 48–76 % with the formulas (48 %: jlc4-7628-f1 with its
  two CPWG coupons, where kisi's coplanar formula is 6.9 % high); 100Z_Diff 92–97 % field, 31–76 % formula. The formula share dropped from v2 (63–83 %) because the grounded coplanar launch is now 6.48 mm per
  side instead of 3 mm, and kisi's coplanar formula is +5.7 % high there. What falls out with the field solver:
  fan-in / taper pieces, traces over antipads, the short piece where the trace meets the connector's tip.
- `check --all` now returns rows for the connector–connector lanes as well (kisi 0.3.1; v2: none); the coupons are
  still judged with `net`.
- **kisi findings of v2, rechecked with kisi 0.3.1:**
  1. KiCad's 0805 capacitor taken for an 0603 (package from the pad pitch): **resolved** – kisi now reads the case size
     from the footprint name (`kisi_si::package::chip_package`); CAPZ_0805 is an 0805.
  2. A shunt capacitor on a signal net ignored by `net`: **resolved** – `net` models shunt parts at their pads (with a
     note that the package parasitics are estimates); the CAPZ nets now show the capacitor.
  3. A plane opening that ends where a track ends sampled as solid plane (3313 launch at 35 Ω): **resolved** – the
     3313 launch is 50 Ω with the field solver along its whole length, and kisi warns that the path lies over a
     cut-out in a layer between the trace and its reference.
  4. `power` without `--pdn` reports "no nominal voltage" for the VDD_* rails (`gaps`: rails-without-voltage):
     expected, the PDN coupons are meant unbiased.
  5. The launch over a plane opening is 25 % high with the formulas (the field solver is right): still a formula weak
     spot.
- Via results (ladder model): see `kisi_check.md` (A group Z rises with the antipad; D group "missing" return path for
  D_NONE; stub resonances in section 2).

## 10. Measurement plan

**Priority (first order):** P1 THRU (every board), CPWG_25 / CPWG_50, A0800, A1200, D_S0p7, D_NONE, PAIR, E_R_G2,
XT_MS (4 layers); THRU, VLV_L3 (stub notch on the PNA-X / PNA), SL_L3, B_L1L6 (6 layers). P2 the rest of the first
order (A1000, D_S2p0, E_R_G0, G_CAV, the 6-layer pair and D coupons), a second copy of each board (build spread).
Later orders: CAPZ and H (assembly), the 8-layer boards, Aisler, the 3313 boards, the TRL set.

| Instrument | Coupons | Settings | Calibration |
|---|---|---|---|
| ENA, 4 ports, 20 GHz | all S-parameter coupons; 4-port coupons with all four ports | linear 10 MHz – 20 GHz, Δf 10 MHz (P370 and TDR need f_k = k·Δf), IFBW 300 Hz (100 Hz for XT and G), −10 … 0 dBm | ECal / SOLT at the cable ends |
| PNA-X, 4 ports | the same to 40 GHz (2.92 mm); priority the stub coupons (8 layers VLV_L3, E_L1L3, VLV_L6; 6 layers VLV_L3), A, D, E | 10 MHz – 40 GHz, Δf 10 MHz (4000 points) | 2.92 mm ECal or mechanical kit at the cable ends (Samtec used a Maury 8770CK) |
| PNA, 2 ports | 2-port coupons; TRL set | 10 MHz – 40 GHz | 2.92 mm SOLT, then on-board multiline TRL |
| VNA 2-port with low-frequency range (e.g. ENA E5061B LF-RF) | H, CAPZ, G (shunt-thru) | log 100 kHz – 100 MHz + linear 10 MHz – 2 GHz (section 6); ground-loop isolator on port 2 | SOLT at the cable ends |
| Scope + step source (TDR/TDT) | THRU (Zc plateau), A / D vias, E (differential), XT / BS / DIFF (NEXT, FEXT, Zdiff plateau) | normalised to a 35 ps Gaussian edge | open / short / load at the cable end |

- **De-embedding:** P370 2×thru with the board's own THRU / PAIR (`sparam.fixture_2xthru`, `deembed2`; pairs: per-port
  shift, or scikit-rf `IEEEP370_MM_NZC_2xThru`). Self-check: LINE_50 de-embedded with THRU is a clean 25 mm line.
- **Repeatability:** remount the connectors on THRU three times; two copies of each board.
- **Stackup extraction first:** εeff and tan δ from LINE_* / SL_L3 (line–line), core εr from G_CAV, a micro-section for
  thicknesses; put the values into `stackups.json`, regenerate with `--reuse-design` and rerun kisi and the 3D cases.

## 11. Ordering checklist

| Item | JLCPCB, **first order** (2026-10-30) | JLCPCB, later (7628) | JLCPCB, later (3313) | Aisler, later |
|---|---|---|---|---|
| Boards | 3 designs: jlc4-7628-f1 **100 × 96**, jlc4-7628-f2 **35 × 156**; jlc6-7628-f1 **50 × 132** (bounding boxes, mm) | 14 designs: 5 × 4 layers (a–d, p), 4 × 6 layers (a–d), 5 × 8 layers (a–d, p) | 8 designs: 4 × 4 layers, 4 × 6 layers | 1: 35 × 144 mm |
| Files | Gerbers + drill from KiCad after refill (B) and DRC, one order line per board | same | same | KiCad upload |
| Stackup | impedance control **on**; templates **JLC04161H-7628**, **JLC06161H-7628**, FR-4 TG155 | + **JLC08201H-7628** (2.0 mm) | **JLC04161H-3313**, **JLC06161H-3313** | ask sales for the stackup first; 35 µm outer if offered |
| Impedance specs | 50 Ω L1 0.345 mm; 100 Ω diff. at the via pitch L1 0.315/0.685; 6 layers In2 stripline 0.405 | + 100 Ω diff. L1 0.205/0.2; 6 layers pair 0.19/0.2; 8 layers In2 stripline 0.21, pair 0.14/0.2 | 50 Ω L1 0.15; diff. 0.115/0.2; 6 layers In2 0.515, pair 0.21/0.2 | – |
| Copper / finish / mask | 1 oz outer, 0.5 oz inner; **ENIG**; green mask both sides | same | same | ENIG, green |
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
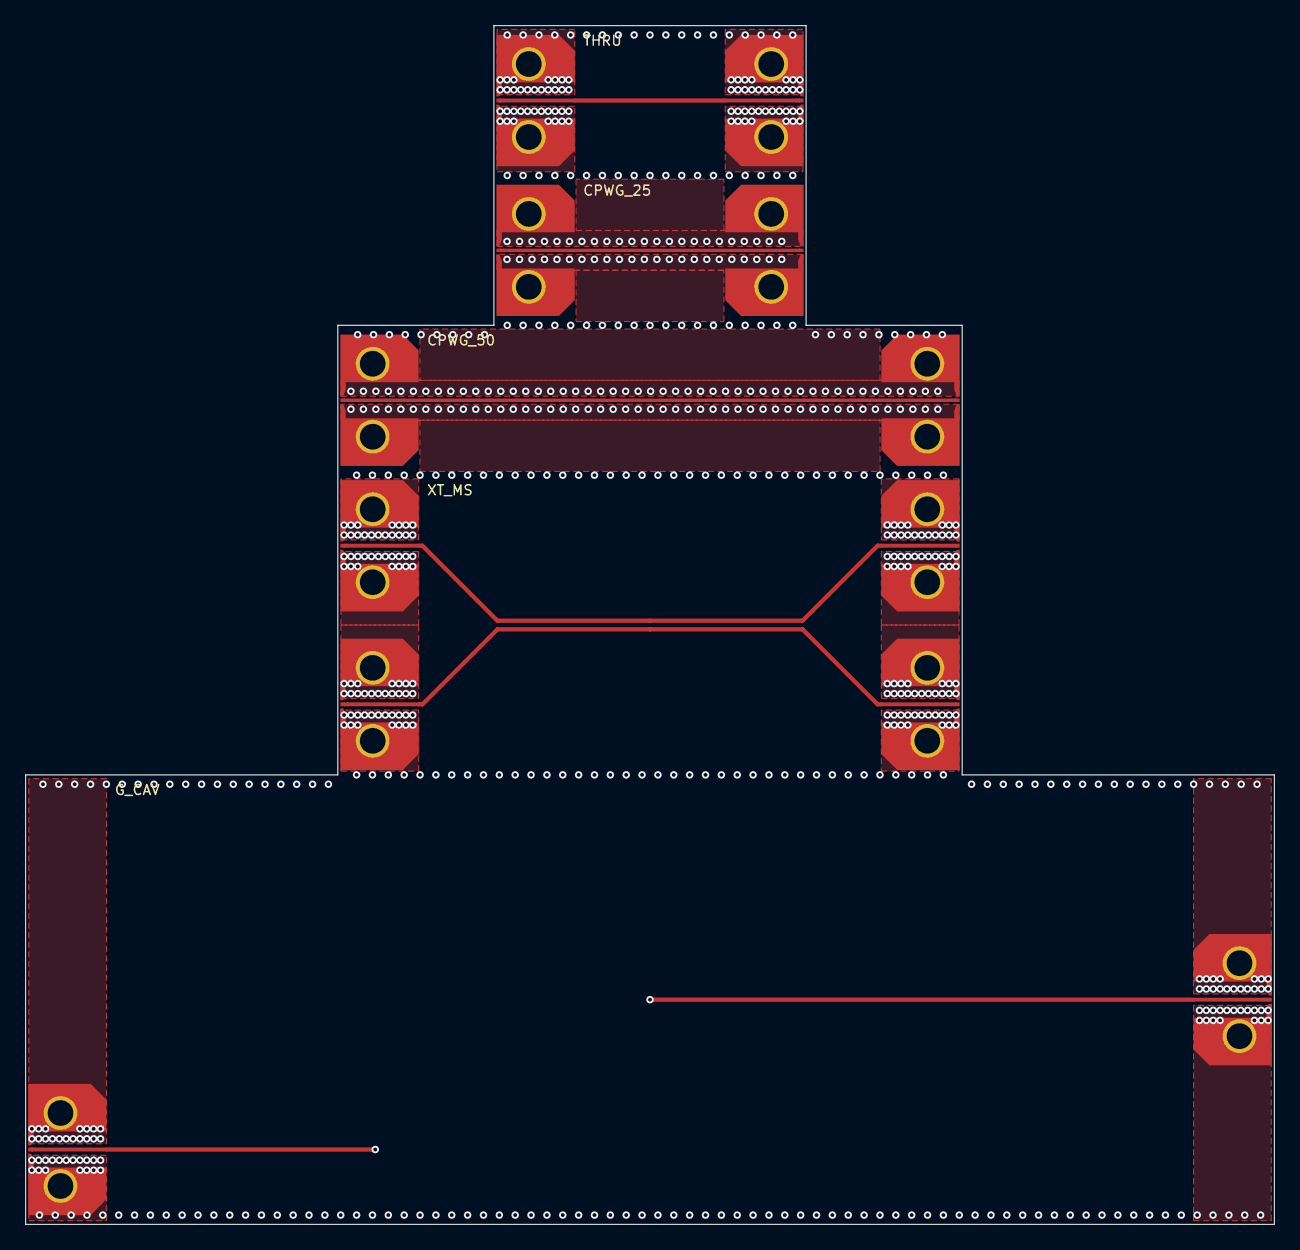
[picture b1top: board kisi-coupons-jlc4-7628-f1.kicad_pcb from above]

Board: 4 copper layers, 100.0 x 96.0 mm, 12 parts (0 on the bottom side), 7 nets.

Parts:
J1, J2, J7, J8, J9, J10, J11, J12: 292-J-P-EP-ST-EL-01; Samtec_292-J-P-EP-ST-EL-01_EdgeLaunch_W0.315
J3, J4, J5, J6: 292-J-P-EP-ST-EL-01; Samtec_292-J-P-EP-ST-EL-01_EdgeLaunch_W0.28

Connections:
CAV_G_CAV: J11.1, J12.1
GND: J1.2, J1.3, J2.2, J2.3, J3.2, J3.3, J4.2, J4.3, J5.2, J5.3, J6.2, J6.3, J7.2, J7.3, J8.2, J8.3, J9.2, J9.3, J10.2, J10.3, J11.2, J11.3, J12.2, J12.3
SE_CPWG_25: J3.1, J4.1
SE_CPWG_50: J5.1, J6.1
SE_THRU: J1.1, J2.1
SE_XT_A: J7.1, J9.1
SE_XT_V: J8.1, J10.1

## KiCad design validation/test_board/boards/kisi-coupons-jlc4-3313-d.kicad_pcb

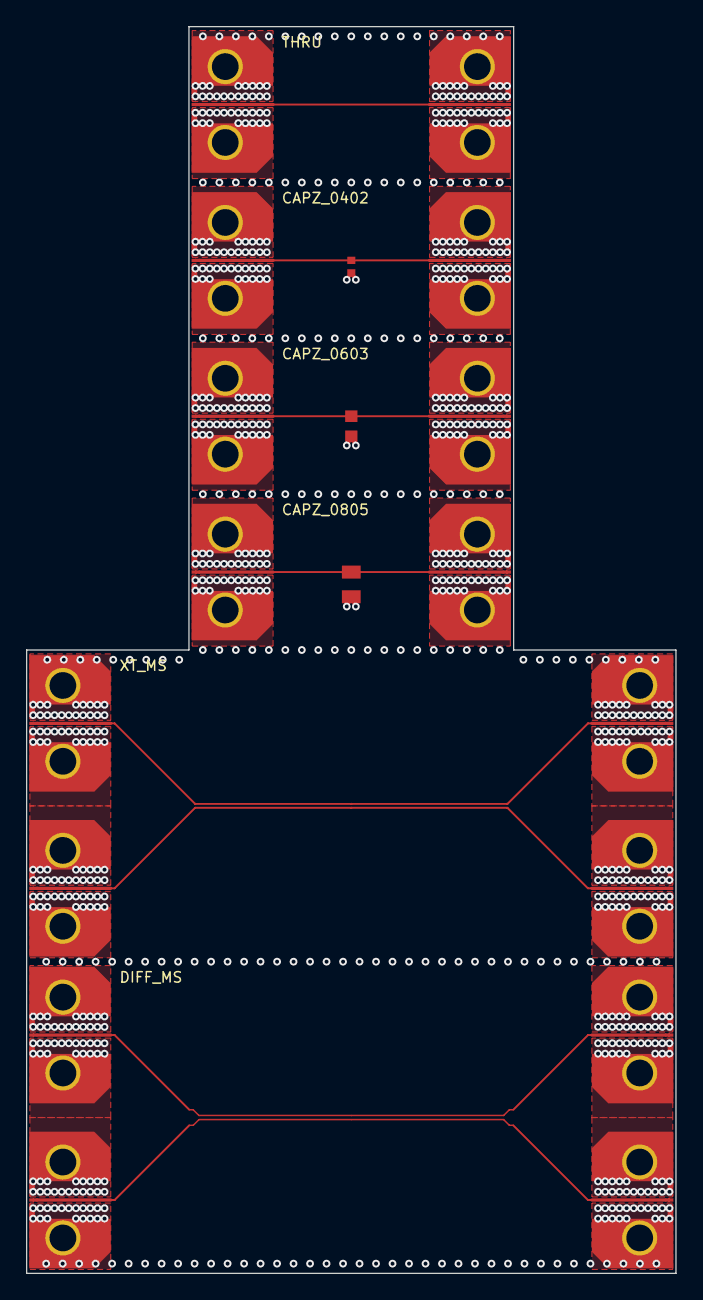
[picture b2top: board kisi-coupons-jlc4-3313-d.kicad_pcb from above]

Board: 4 copper layers, 50.0 x 96.0 mm, 19 parts (0 on the bottom side), 9 nets.

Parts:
C1: 100nF 16V X7R; C_0402_1005Metric_V
C2: 100nF 16V X7R; C_0603_1608Metric_V
C3: 100nF 16V X7R; C_0805_2012Metric_V
J1, J2, J3, J4, J5, J6, J7, J8, J9, J10, J11, J12, J13, J14, J15, J16: 292-J-P-EP-ST-EL-01; Samtec_292-J-P-EP-ST-EL-01_EdgeLaunch_W0.255

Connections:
DP_DIFF_MS_N: J14.1, J16.1
DP_DIFF_MS_P: J13.1, J15.1
GND: C1.2, C2.2, C3.2, J1.2, J1.3, J2.2, J2.3, J3.2, J3.3, J4.2, J4.3, J5.2, J5.3, J6.2, J6.3, J7.2, J7.3, J8.2, J8.3, J9.2, J9.3, J10.2, J10.3, J11.2, J11.3, J12.2, J12.3, J13.2, J13.3, J14.2, J14.3, J15.2, J15.3, J16.2, J16.3
SE_CAPZ_0402: C1.1, J3.1, J4.1
SE_CAPZ_0603: C2.1, J5.1, J6.1
SE_CAPZ_0805: C3.1, J7.1, J8.1
SE_THRU: J1.1, J2.1
SE_XT_A: J9.1, J11.1
SE_XT_V: J10.1, J12.1

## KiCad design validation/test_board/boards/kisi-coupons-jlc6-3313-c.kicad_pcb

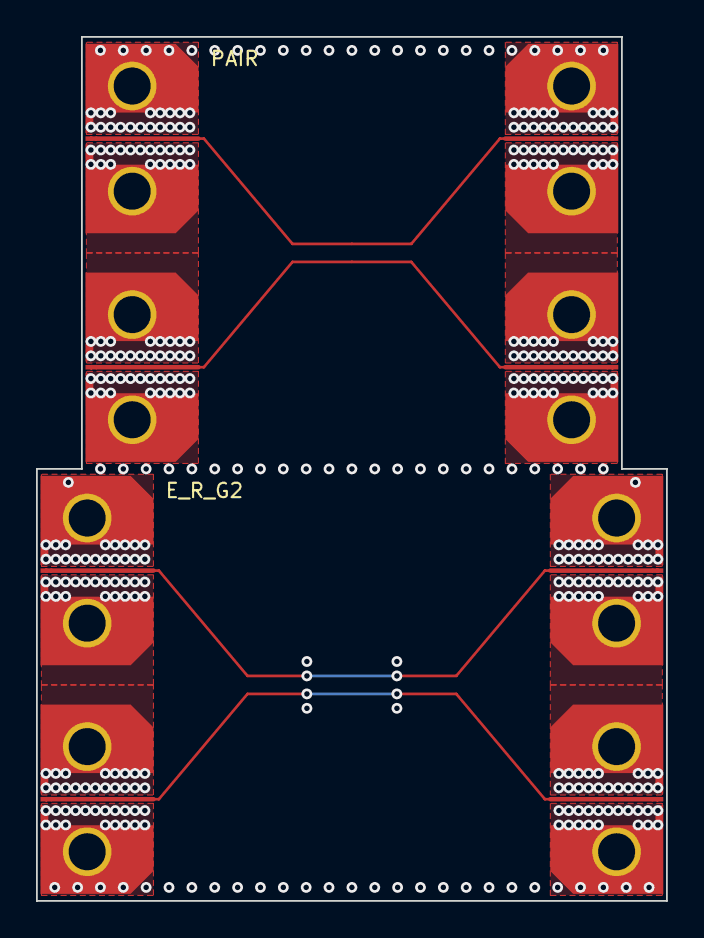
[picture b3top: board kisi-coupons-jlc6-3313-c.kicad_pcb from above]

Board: 6 copper layers, 35.0 x 48.0 mm, 8 parts (0 on the bottom side), 5 nets.

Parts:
J1, J2, J3, J4, J5, J6, J7, J8: 292-J-P-EP-ST-EL-01; Samtec_292-J-P-EP-ST-EL-01_EdgeLaunch_W0.255

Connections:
DP_E_R_G2_N: J6.1, J8.1
DP_E_R_G2_P: J5.1, J7.1
DP_PAIR_N: J2.1, J4.1
DP_PAIR_P: J1.1, J3.1
GND: J1.2, J1.3, J2.2, J2.3, J3.2, J3.3, J4.2, J4.3, J5.2, J5.3, J6.2, J6.3, J7.2, J7.3, J8.2, J8.3
